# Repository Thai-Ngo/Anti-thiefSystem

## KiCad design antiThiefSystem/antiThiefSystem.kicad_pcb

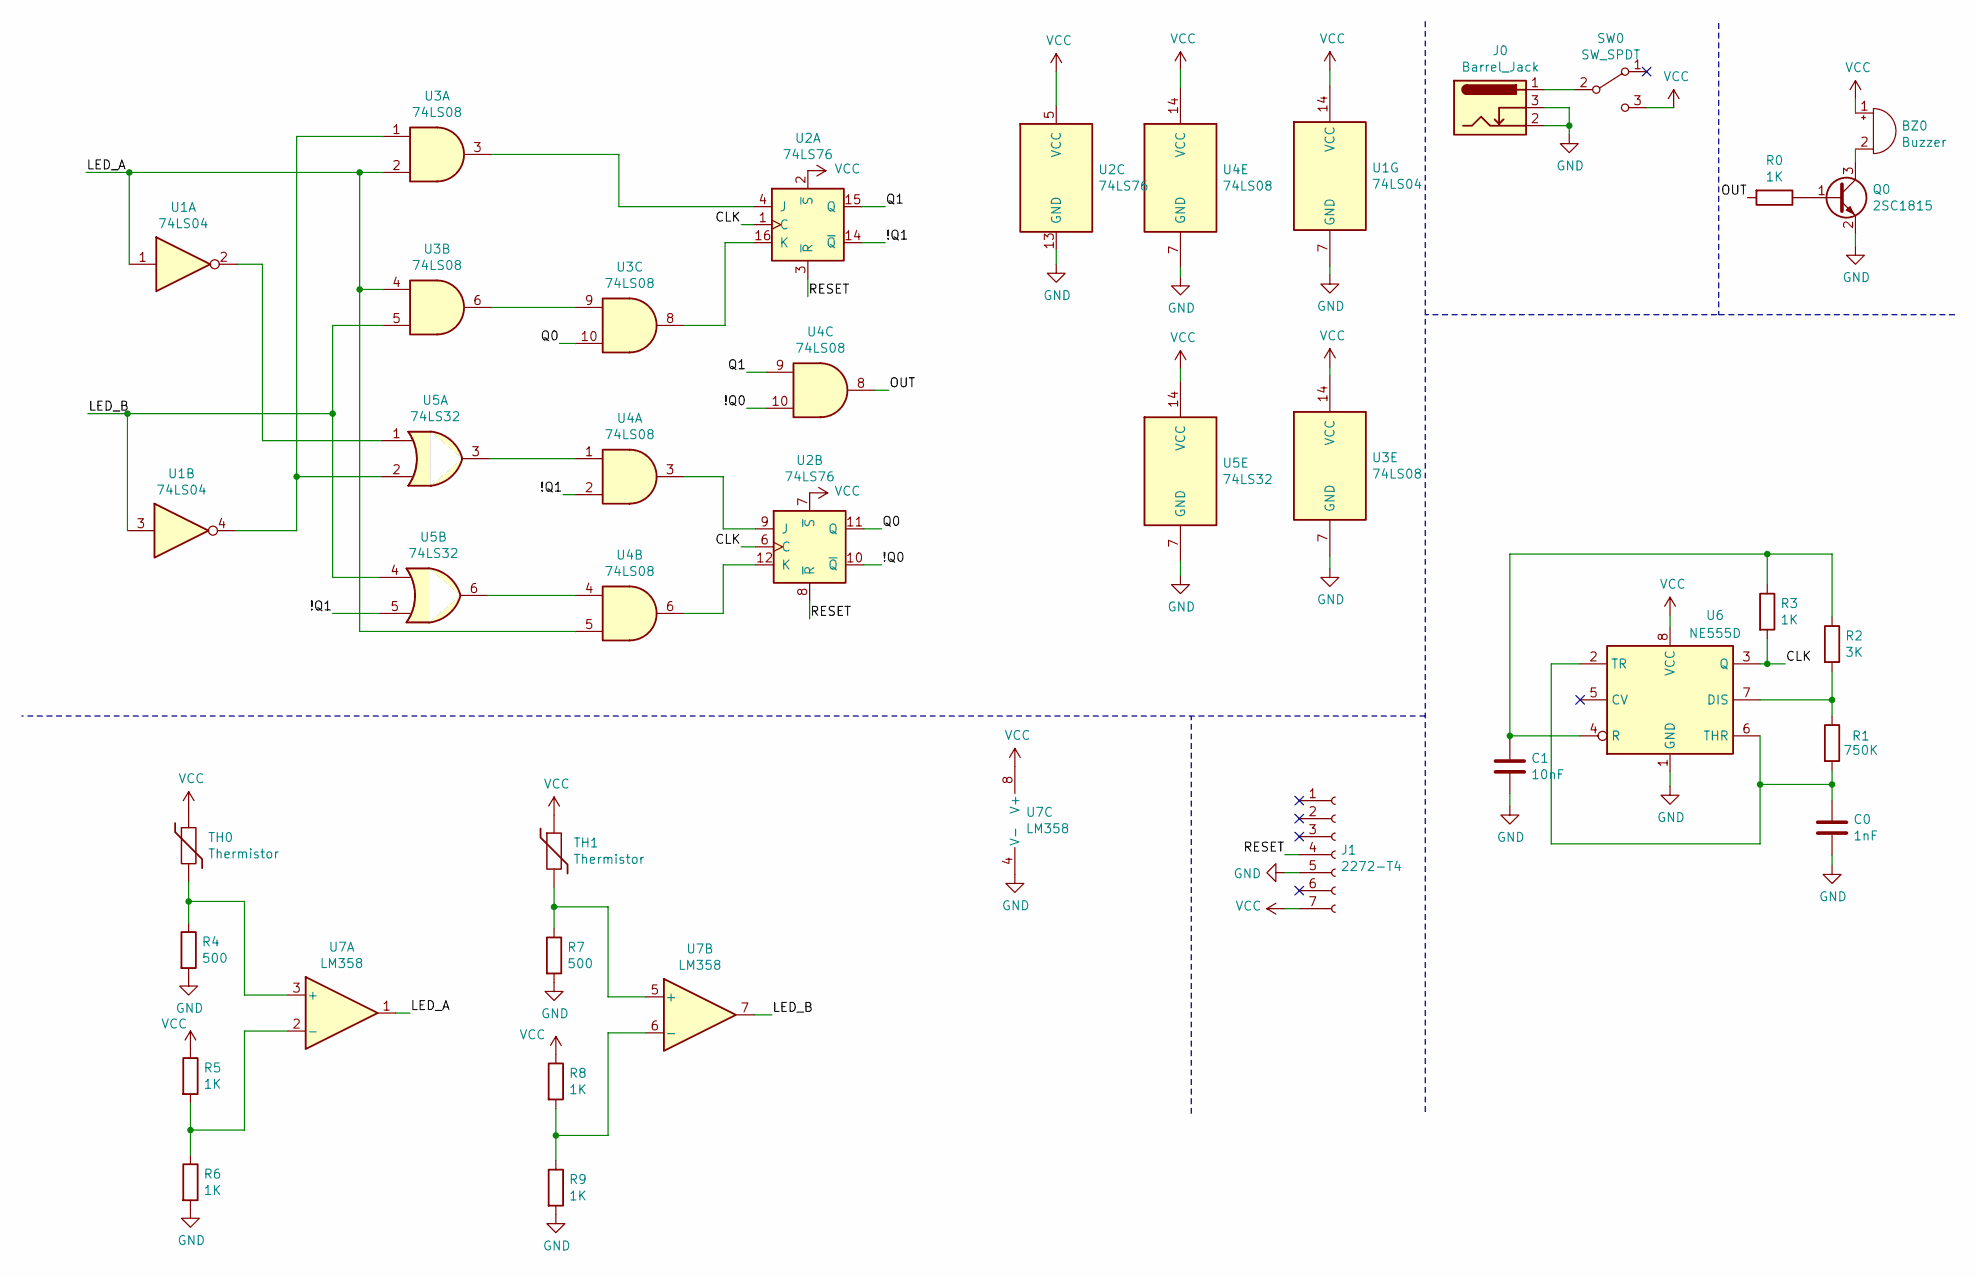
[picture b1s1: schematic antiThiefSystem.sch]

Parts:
BZ0: Buzzer; Buzzer_12x9.5RM7.6
C0: 1nF; C_1206_3216Metric
C1: 10nF; C_1206_3216Metric
J0: Barrel_Jack; BarrelJack_Horizontal
J1: 2272-T4; PinSocket_1x07_P2.54mm_Vertical
Q0: 2SC1815; TO-92L_Inline_Wide
R0, R3, R5, R6, R8, R9: 1K; R_1206_3216Metric
R1: 750K; R_1206_3216Metric
R2: 3K; R_1206_3216Metric
R4, R7: 500; R_1206_3216Metric
SW0: SW_SPDT; SS-12D11
TH0, TH1: Thermistor; PinSocket_1x02_P2.54mm_Vertical
U1: 74LS04; DIP-14_W7.62mm_Socket
U2: 74LS76; DIP-16_W7.62mm_Socket
U3, U4: 74LS08; DIP-14_W7.62mm_Socket
U5: 74LS32; DIP-14_W7.62mm_Socket
U6: NE555D; DIP-8_W7.62mm_Socket
U7: LM358; DIP-8_W7.62mm_Socket

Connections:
/!Q0: U2.10 (~Q), U4.10
/!Q1: U2.14 (~Q), U4.2, U5.5
/CLK: R3.2, U2.1 (C), U2.6 (C), U6.3 (Q)
/LED_A: U1.1, U3.2, U3.4, U4.5, U7.1
/LED_B: U1.3, U3.5, U5.4, U7.7
/OUT: R0.2, U4.8
/Q0: U2.11 (Q), U3.10
/Q1: U2.15 (Q), U4.9
/RESET: J1.4, U2.3 (~R), U2.8 (~R)
GND: C0.2, C1.1, J0.2, J0.3, J1.5, Q0.2 (E), R4.2, R6.2, R7.2, R9.2, U1.7 (GND), U2.13 (GND), U3.7 (GND), U4.7 (GND), U5.7 (GND), U6.1 (GND), U7.4 (V-)
unnamed: BZ0.2 (+), Q0.3 (C)
unnamed: C0.1, R1.2, U6.2 (TR), U6.6 (THR)
unnamed: C1.2, R2.1, R3.1, U6.4 (R)
unnamed: J0.1, SW0.2 (B)
unnamed: Q0.1 (B), R0.1
unnamed: R1.1, R2.2, U6.7 (DIS)
unnamed: R4.1, TH0.2, U7.3 (+)
unnamed: R5.2, R6.1, U7.2 (-)
unnamed: R7.1, TH1.2, U7.5 (+)
unnamed: R8.2, R9.1, U7.6 (-)
unnamed: U1.2, U5.1
unnamed: U1.4, U3.1, U5.2
unnamed: U2.4 (J), U3.3
unnamed: U2.9 (J), U4.3
unnamed: U2.12 (K), U4.6
unnamed: U2.16 (K), U3.8
unnamed: U3.6, U3.9
unnamed: U4.1, U5.3
unnamed: U4.4, U5.6
VCC: BZ0.1 (-), J1.7, R5.1, R8.1, SW0.3 (C), TH0.1, TH1.1, U1.14 (VCC), U2.2 (~S), U2.5 (VCC), U2.7 (~S), U3.14 (VCC), U4.14 (VCC), U5.14 (VCC), U6.8 (VCC), U7.8 (V+)

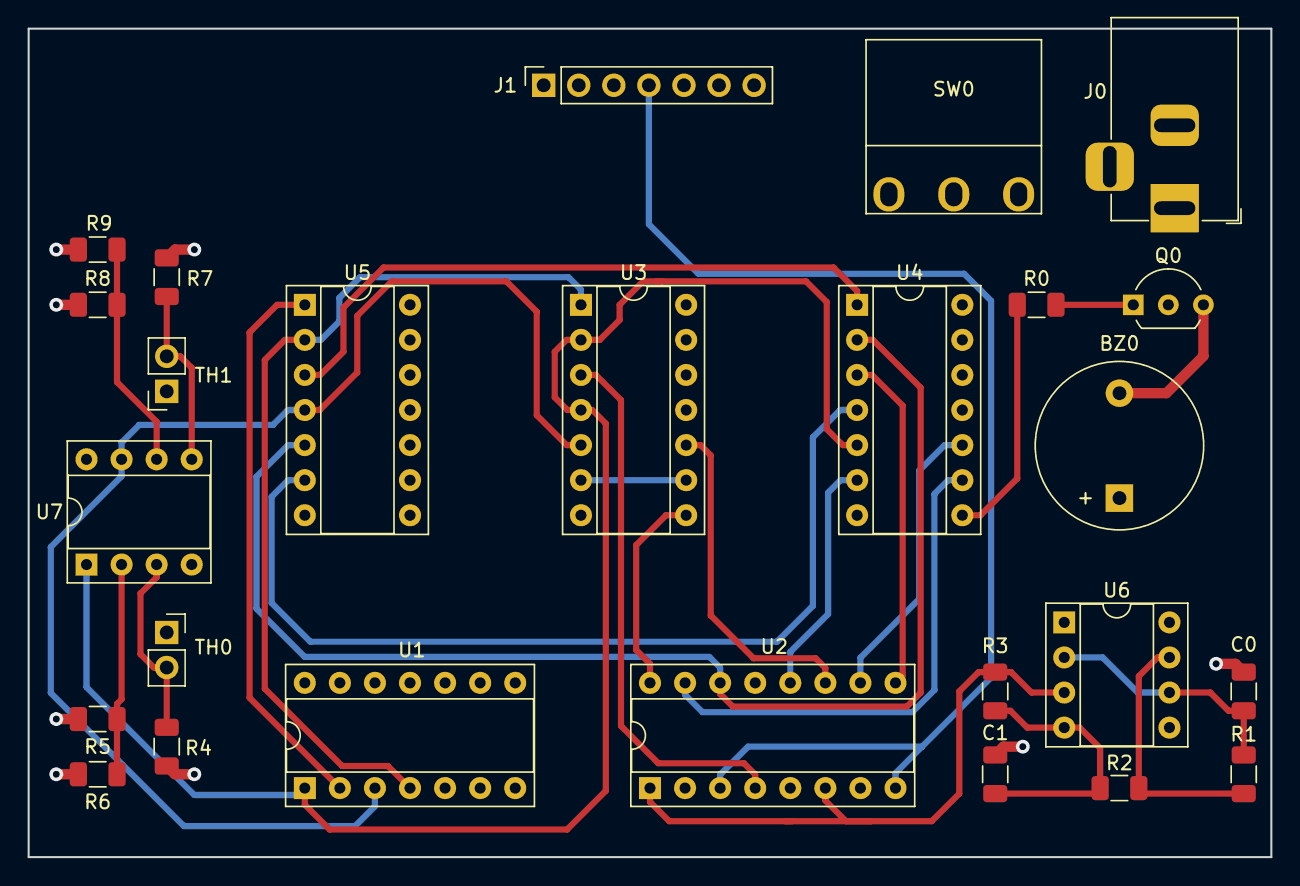
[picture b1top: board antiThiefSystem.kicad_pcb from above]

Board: 4 copper layers, 90.0 x 60.0 mm, 26 parts (0 on the bottom side), 30 nets.

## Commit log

2021-10-05 Create project and add logic block
2021-10-05 Add power block, clock block and input block
2021-10-06 Draw PCB not completely
2021-10-07 Finish PCB
2021-10-07 Edit photoresistor footprint
